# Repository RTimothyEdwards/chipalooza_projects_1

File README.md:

# Caravel Analog User

---

| :exclamation: Important Note            |
|-----------------------------------------|

This is the first test chip from the Chipalooza challenge 2024.
11 designs made it on the April tapeout.

The projects on this tapeout and their source URLs are as follows:

	1.  	High-speed crystal oscillator (4-16MHz)
		hsxo-cpz1 
		https://github.com/efabless/sky130_ht_ip__hsxo_cpz1 (forked)
		https://github.com/htfab/hsxo-cpz1
		Tamas Hubai

	2.  	Brownout detector
		sky130_ajc_ip__brownout
		https://github.com/efabless/sky130_ajc_ip__brownout (forked)
		https://github.com/ajcci/sky130_ajc_ip__brownout
		Robin Tsang

	3.  	Overvoltage detector
		sky130_ajc_ip__overvoltage
		https://github.com/efabless/sky130_ajc_ip__overvoltage (forked)
		https://github.com/ajcci/sky130_ajc_ip__overvoltage
		Robin Tsang

	4.  	Power-on-Reset
		sky130_ajc_ip__por
		https://github.com/efabless/sky130_ajc_ip__por (forked)
		https://github.com/ajcci/sky130_ajc_ip__por
		Robin Tsang

	5.  	Comparator
		sky130_ak_ip__comparator
		https://github.com/efabless/sky130_ak_ip__comparator (forked)
		https://github.com/andrewkkang/sky130_ak_ip__comparator
		Andrew Kang

	6.  	Low-speed crystal oscillator (32kHz)
		sky130_be_ip__lsxo
		https://github.com/efabless/sky130_be_ip__lsxo (forked)
		https://github.com/b-etz/sky130_be_ip__lsxo
		Brady Etz

	7.  	Temperature sensor
		sky130_od_ip__tempsensor
		https://github.com/efabless/sky130_od_ip__tempsensor (forked)
		https://github.com/ordicker/sky130_od_ip__tempsensor
		Or Dicker

	8.  	Low power operational amplifier
		sky130_rodovalho_ip__lpopamp
		https://github.com/efabless/sky130_rodovalho_ip__lpopamp (forked)
		https://github.com/lhrodovalho/sky130_rodovalho_ip__lpopamp
		Luis Henrique Rodovalho

	9.  	High gain-bandwidth operational amplifier
		sky130_td_ip__opamp_hp
		https://github.com/efabless/sky130_td_ip__opamp_hp (forked)
		https://github.com/tdextrous/sky130_td_ip__opamp_hp
		Thomas Dexter

	10. 	Overvoltage detector
		sky130_vbl_ip__overvoltage
		https://github.com/efabless/sky130_vbl_ip__overvoltage (forked)
		https://github.com/LDFranck/sky130_vbl_ip__overvoltage
		Lucas Franck, William Orlato, and Toni Tejada

	11.	Bandgap (not from Chipalooza)
		bandgap
		https://github.com/efabless/sky130_cw_ip (forked)
		https://github.com/christoph-weiser/mpw7
		Christoph Weiser

	12.	Power FET (not from Chipalooza)
		power_stage
		(in this repository)
		Weston Braun

	13.	Bias current generator (not from Chipalooza)
		bias_generator
		(in this repository)
		Tim Edwards

	14.	Ground-isolated analog switch (not from Chipalooza)
		isolated_switch_ena1v8
		(in this repository)
		Tim Edwards

(Documentation, including test instructions, still needs to be completed)

:---: | :---

Building:

Get the dependencies above by doing "make get_ip_blocks" in the top level
directory.  This will clone all of the IP blocks from various github
repository sources into the "dependencies" directory.

The test chip is generated in magic by running magic in the mag/ directory
and issuing the command "source construct_testchip.tcl".

Verifying:

In the top level directory, do "make run-precheck".  This requires at
least setting environment variables PDK_ROOT, PDK, and PRECHECK_ROOT.
If the PDK is installed with open_pdks, then PRECHECK_ROOT can be set
to open_pdks/sources/precheck_sky130.

This might take an hour. If you just want to see the results then you
can download [a tar of the full output](https://github.com/qpwo/_patch_chipalooza_projects_1/releases/tag/build4d31885)

Testing:

All projects are connected either to the logic analyzer (128 I/O bits) or
the GPIO pins.  Generally speaking, static control bits (enable and trim,
for example) are logic analyzer outputs.  Dynamic digital bits are routed
to GPIO digital outputs, while analog I/O are routed to the analog
connections of the GPIO.

Each power supply is routed through gated power pFETs so each project
can be powered individually.  Each power supply connection internally
is routed to a bare analog pin for monitoring the supply voltage of
the project.  Be aware that these are ESD-sensitive points!

Power supplies are enabled through a differential switch.  Due to
time constraints, the differential signals (enable, !enable) were
both routed to the logic analyzer.  Both bits need to be set
correctly.

Most projects take current biases which are distributed by a central
bias current generator circuit.  Various test point bias currents are
connected through ground-isolated switches to GPIO analog signals.

Project circuit blocks are described below, starting at the top left
corner of the chip and working counterclockwise around the chip
perimeter.

---

High Gain-Bandwidth Operational Amplifier  
(Thomas Dexter)  
Enable:  la_data_in[37]  
Bias:    100nA	when selected  
	Selection: la_data_in[40] = 0  
Upstream analog power supply: vdda2/vssa2  
Upstream digital power supply: vccd2/vssd2  
Power supply monitor:  io_analog[10] (pin GPIO 24) "mon_hgbw_opamp"  
Power supply enable: la_data_in[60]  
Amp output:  gpio_noesd[7] (pin GPIO 25) "hgbw_opamp_out"  
Amp negative input: gpio_analog[8] (pin GPIO 26) "hgbw_opamp_in-" when selected  
	Selection: la_data_in[36] = 1  
Amp positive input: gpio_analog[9] (pin GPIO 27) "hgbw_opamp_in+" when selected  
	Selection: la_data_in[34] = 1  

---

Temperature sensor  
(Or Dicker)  
Enable: la_data_in[35]  
Bias:  gpio_noesd[2] (pin GPIO 9) "1.2V_bias" (nominally 1.2V) when selected  
	Selection: la_data_in[122] = 1  
Upstream digital power supply: vccd2/vssd2  
Power supply monitor: io_analog[9] (pin GPIO 23) "mon_temp_sense"  
Power supply enable: la_data_in[58]  
Vbe1_out: gpio_analog[9] (pin GPIO 27) "temp_sense_vbe1" when selected  
	Selection: la_data_in[34] = 0  
Vbe2_out: gpio_analog[8] (pin GPIO 26) "temp_sense_vbe2" when selected  
	Selection: la_data_in[36] = 0  

---

Comparator  
(Andrew Kang)  
Enable: la_data_in[28]  
Hysteresis: la_data_in[29:30]  
Trim: la_data_in[25:27],la_data_in[33:31]  
Bias:	400nA	when selected  
	Selection:  la_data_in[44] = 0  
Upstream analog power supply: vdda2/vssa2  
Upstream digital power supply: vccd2/vssd2  
Power supply monitor: io_analog[8] (pin GPIO 22) "mon_comparator"  
Power supply enable: la_data_in[56]  
Comparator output: io_out[17] (pin GPIO 28) "comparator_out"  
Comparator negative input:  gpio_analog[12] (pin GPIO 30) "comparator_in-" when selected  
	Selection: la_data_in[22] = 1  
Comparator positive input:  gpio_analog[11] (pin GPIO 29) "comparator_in+" when selected  
	Selection: la_data_in[23] = 1  
	
---

Low power operational amplifier  
(Luis Henrique Rodovalho)  
Enable: la_data_in[21]  
Bias:  10uA when selected  
	Selection:  la_data_in[46] = 0  
Upstream analog power supply: vdda2/vssa2  
Upstream digital power supply: vccd2/vssd2  
Power supply monitor: io_analog[7] (pin GPIO 21) "mon_lpopamp"  
Power supply enable: la_data_in[54]  
Amplifier output:  gpio_analog[13] (pin GPIO 31) "lpopamp_out"  
Amplifier negative input: gpio_analog[11] (pin GPIO 29) "lpopamp_in-" when selected  
	Selection: la_data_in[23] = 0  
Amplifier positive input: gpio_analog[12] (pin GPIO 30) "lpopamp_in+" when selected  
	Selection: la_data_in[22] = 0  

---

High speed crystal oscillator  
(Tamas Hubai)  
Enable: la_data_in[19]  
Standby: la_data_in[20]  
Bias:  10uA when selected  
	Selection: la_data_in[47] = 0  
Upstream analog power supply: vdda2/vssa2  
Upstream digital power supply: vccd2/vssd2  
Power supply monitor: io_analog[6] (pin GPIO 20) "mon_hsxo"  
Power supply enable:  la_data_in[52]  
Oscillator out:  io_out[23] (pin GPIO 34) "hsxo_out"  
Crystal Xin:  gpio_analog[14] (pin GPIO 32) "hsxo_xin"  
Crystal Xout: gpio_analog[15] (pin GPIO 33) "hsxo_xout"  

---

Bandgap (Christoph Weiser)  
Enable: none (enable via power supply)  
Bias:  self-biased  
Trim: la_data_in[9,8,10,7,11,6,12,5,13,4,14,3,15,2,16,1]  
Upstream digital power supply: vccd2/vssd2  
Power supply monitor: io_analog[5] (pin GPIO 19) "mon_bandgap"  
Power supply enable: la_data_in[50]  
Bandgap output:  gpio_analog[16] (pin GPIO 34) "bandgap_out" when selected  
	Selection:  la_data_in[18] = 1  

---

Brownout detector (Robin Tsang)  
Enable: la_data_in[109]  
Bias: gpio_noesd[2] (pin GPIO 9) "1.2V_bias" (nominally 1.2V) when selected  
	Selection: la_data_in[122] = 0  
Bias: 200nA when selected  
	Selection: la_data_in[43] = 0  
Trip point select (otrip):  la_data_in[112:113,111]  
Trip point select (vtrip):  la_data_in[107:106,108]  
Force enable RC osc: la_data_in[115]  
Force disable RC osc: la_data_in[114]  
Force short oneshot: la_data_in[116]  
Current source select: la_data_in[110]  
Upstream analog power supply: vdda1/vssa1  
Upstream digital power supply: vccd1/vssd1  
Power supply monitor: io_analog[0] (pin GPIO 14) "mon_brownout"  
Power supply enable: la_data_in[77]  
Outb: io_out[0] (pin GPIO 0) "brownout_outb"  
Dcomp: io_out[1] (pin GPIO 1) "brownout_dcomp"  
Vunder: io_out[5] (pin GPIO 5) "brownout_vunder"  
Timed out: la_data_out[117]  

---

Overvoltage detector (Robin Tsang)  
Enable: la_data_in[100]  
Bias: gpio_noesd[2] (pin GPIO 9) "1.2V_bias" (nominally 1.2V) when selected  
	Selection: la_data_in[122] = 0  
Bias: 200nA when selected  
	Selection: la_data_in[42] = 0  
Trip point select (otrip):  la_data_in[105:102]  
Current source select: la_data_in[101]  
Upstream analog power supply: vdda1/vssa1  
Upstream digital power supply: vccd1/vssd1  
Power supply monitor: io_analog[1] (pin GPIO 15) "mon_overvoltage1"  
Power supply enable: la_data_in[75]  
Ovout: io_out[6] (pin GPIO 6) "overvoltage1_ovout"  

---

Power-on-reset (Robin Tsang)  
Bias: gpio_noesd[2] (pin GPIO 9) "1.2V_bias" (nominally 1.2V) when selected  
	Selection: la_data_in[122] = 0  
Bias: 200nA when selected  
	Selection: la_data_in[41] = 0  
Trip point select (otrip): la_data_in[96:98]  
Force PDN: la_data_in[94]  
Force enable RC osc: la_data_in[93]  
Force disable RC osc: la_data_in[92]  
Force short oneshot: la_data_in[99]  
Current source select: la_data_in[95]  
Upstream analog power supply: vdda1/vssa1  
Upstream digital power supply: vccd1/vssd1  
Power supply monitor: io_analog[2] (pin GPIO 16) "mon_por"  
Power supply enable: la_data_in[73]  
POR: io_out[7] (pin GPIO 7) "por_out"  
PORb: io_out[8] (pin GPIO 8) "por_outb"  
Osc_clk: io_out[3] (pin GPIO 3) "por_osc_clk"  
Dcomp: io_out[2] (pin GPIO 2) "por_dcomp"  
Pwup_filt: io_out[4] (pin GPIO 4) "por_pwup_filt"  
Startup timed out: la_data_out[120]  
POR timed out: la_data_out[119]  

---

Low-speed (32kHz) crystal oscillator (Brady Etz)  
Enable: la_data_in[86]  
Standby: la_data_in[85]  
Bias: 50nA when selected  
	Selection: la_data_in[39] = 0  
Upstream analog power supply: vdda1/vssa1  
Upstream digital power supply: vccd1/vssd1  
Power supply monitor: io_analog[3] (pin GPIO 17) "mon_lsxo"  
Power supply enable: la_data_in[69]  
Dout: io_out[12] (pin GPIO 12) "lsxo_out"  
Crystal XIn: gpio_noesd[3] (pin GPIO 10) "lsxo_xin"  
Crystal XOut: gpio_noesd[4] (pin GPIO 11) "lsxs_xout"  

---

Overvoltage detector (Lucas Franck & William Orlato)  
Enable: la_data_in[91]  
Bias: gpio_noesd[2] (pin GPIO 9) "1.2V_bias" (nominally 1.2V) when selected  
	Selection: la_data_in[122] = 1  
Bias: 600nA when selected  
	Selection: la_data_in[45] = 0  
Trip point select (vtrip): la_data_in[87:90]  
Upstream analog power supply: vdda1/vssa1  
Upstream digital power supply: vccd1/vssd1  
Power supply monitor: io_analog[4] (pin GPIO 18) "mon_overvoltage2"  
Power supply enable: la_data_in[65]  
OVout: io_out[13] (pin GPIO 13) "overvoltage2_out"  

---

All bias currents are regulated by an input bias voltage which is
nominally 3.3V but may be adjusted up or down to trim the bias
(limit max. voltage VDDIO + 0.3V to avoid forward biasing the ESD
diodes into the power supply).  
Bias in: gpio_analog[17] (pin GPIO 35) "bias_trim_in"  

---

Three power FETs are unused but should be kept disabled:  
Enable:  la_data_in[62], la_data_in[67], la_data_in[71]  

---

The bias generator has a master enable signal that will enable
all bias currents:  

Enable bias generator:  la_data_in[79]   

It also has a separate disable signal for the sources (which is
all of the biases used by projects on this chip):  

Disable bias generator sources:  la_data_in[48]   

---

These current sources/sinks are multiplexed to analog pins not otherwise
being used for projects.  The "enable" or "disable" bit enables or disables
the current bias, and "selection" connects it to the associated pin:  

100nA source (test0): gpio_analog[16] (pin GPIO 34) when selected  
	Disable: la_data_in[49]  
	Selection: la_data_in[18] = 0 (at pin)  

100nA source (test1): gpio_analog[10] (pin GPIO 28) when selected  
	Disable: la_data_in[38]  
	Selection: la_data_in[17] = 1 (at pin)  

100nA sink (test1): gpio_analog[6] (pin GPIO 13) when selected  
	Enable:  la_data_in[84]  
	Selection: la_data_in[124] = 1 (at pin)  

3.7uA sink (sink_3700): gpio_analog[5] (pin GPIO 12) when selected  
	Enable:  la_data_in[83]  
	Selection: la_data_in[123] = 1 (at pin)  

5.0uA sink (sink_5000_1): gpio_analog[1] (pin GPIO 8) when selected  
	Enable:  la_data_in[81]  
	Selection: la_data_in[121] = 1 (at pin)  

100nA sink (test0): gpio_analog[0] (pin GPIO 7) when selected  
	Enable:  la_data_in[78]  
	Selection: la_data_in[118] = 1 (at pin)  

---

Refer to [README](docs/source/index.rst) for this sample project documentation.   

Refer to docs/chipalooza_testchip1.pdf (.ps) for a package pinout drawing.  

---

Chip QFN-64 package pinout:

Pin  Signal(s)  
 1   vssa2  
 2   mprj_io[25] hgbw_opamp_out  
 3   mprj_io[26] hgbw_opamp_in- temp_sense_vbe2  
 4   mprj_io[27] hgbw_opamp_in+ temp_sense_vbe1  
 5   mprj_io[28] comparator_out source_100_1  
 6   mprj_io[29] comparator_in+ lpopamp_in-  
 7   mprj_io[30] comparator_in- lpopamp_in+  
 8   mprj_io[31] lpopamp_out  
 9   vdda2  
10   vssd2  
11   mprj_io[32] hsxo_xin  
12   mprj_io[33] hsxo_xout  
13   mprj_io[34] hsxo_out  bandgap_out source_100_0  
14   mprj_io[35] bias_trim_in  
15   mprj_io[36]  
16   mprj_io[37]  
17   vddio  
18   vccd  
19   N/C  
20   vssa  
21   resetb  
22   clock  
23   vssd  
24   flash_csb  
25   flash_clk  
26   flash_io0  
27   flash_io1  
28   gpio  
29   vssio  
30   vdda  
31   mprj_io[0] brownout_outb  
32   mprj_io[1] brownout_dcomp  
37   mprj_io[2] por_dcomp  
34   mprj_io[3] por_osc_clk  
35   mprj_io[4] por_pwup_filt  
36   mprj_io[5] brownout_vunder  
37   mprj_io[6] overvoltage1_ovout  
38   vssa1  
39   vssd1  
40   vdda1  
41   mprj_io[7] por_out  sink_100_0  
42   mprj_io[8] por_outb  
43   mprj_io[9]  1.2V_bias  
44   mprj_io[10] lsxo_xin  
45   mprj_io[11] lsxo_xout  
46   mprj_io[12] lsxo_out  sink_3700  
47   vdda1  
48   mprj_io[13] overvoltage2_out  sink_100_1  
49   vccd1  
50   mprj_io[14] mon_brownout  
51   mprj_io[15] mon_overvoltage1  
52   vssa1  
53   mprj_io[16] mon_por  
54   mprj_io[17] mon_lsxo  
55   mprj_io[18] mon_overvoltage2  
56   vssio  
57   mprj_io[19] mon_bandgap  
58   mprj_io[20] mon_hsxo  
59   mprj_io[21] mon_lpopamp  
60   mprj_io[22] mon_comparator  
61   mprj_io[23] mon_temp_sense  
62   mprj_io[24] mon_hgbw_opamp  
63   vccd2  
64   vddio  

---

NOTES:  The following pins have dual analog and digital functions.  The
analog function is enabled/disabled by a ground isolation swtch, and the
digital function is enabled/disabled by configuring the GPIO from
software.

pin 41:  por_out (digital), sink_100_0 (analog)  
pin 42:  porb_out (digital), sink_5000_1 (analog)  
pin 46:  lsxo_out (digital), sink_3700 (analog)  
pin 5:   comparator_out (digital), source_100_1 (analog)  
pin 13:  hsxo_out (digital), bandgap_out, source_100_0 (analog, multiplexed)*  

*Because the analog on pin 13 is multiplexed, the analog can only be
 completely disabled by selecting source_100_0 as the multiplexer input and
 then disabling the current source.  This is not ideal but should not
 interfere with the HSXO output.

---

Logic analyzer map:

la_data_in[16:1]  Bandgap trim (not in order)  
la_data_in[17]	  Select source_test_1 at pin  
la_data_in[18]    Select bandgap_out (1) or source_test_0 (0)  
la_data_in[19]	  HSXO enable  
la_data_in[20]	  HSXO standby  
la_data_in[21]	  LP opamp enable  
la_data_in[22]	  Select comparator_in- (1) or lpopamp_in+ (0)  
la_data_in[23]	  Select comparator_in+ (1) or lpopamp_in- (0)  
la_data_in[27:25] Comparator trim  
la_data_in[28]	  Comparator enable  
la_data_in[30:29] Comparator hysteresis  
la_data_in[33:31] Comparator trim  
la_data_in[34]	  Select hgbw_opamp_in+ (1) or temp_sense_vbe1 (0)  
la_data_in[35]	  Temperature sensor enable  
la_data_in[36]	  Select hgbw_opamp_in- (1) or temp_sense_vbe2 (0)  
la_data_in[37]	  HGBW op amp enable  
la_data_in[38]	  Disable source_test_1 at bias  
la_data_in[39]	  Disable LSXO 50nA bias  
la_data_in[40] 	  Disable HGBW op amp 100nA bias  
la_data_in[41] 	  Disable POR 200nA bias  
la_data_in[42]	  Disable Overvoltage1 200nA bias  
la_data_in[43]	  Disable Brownout 200nA bias  
la_data_in[44]	  Disable Comparator 400nA bias  
la_data_in[45]	  Disable Overvoltage2 600nA bias  
la_data_in[46]	  Disable LP op amp 10uA bias  
la_data_in[47]	  Disable HSXO 10uA bias  
la_data_in[48] 	  Disable bias generator sources  
la_data_in[49]	  Disable source_test_0  
la_data_in[50]	  Enable Bandgap power supply  
la_data_in[52]	  Enable HSXO power supply  
la_data_in[54]	  Enable LP op amp power supply  
la_data_in[56]	  Enable Comparator power supply  
la_data_in[58]	  Enable Temperature sensor power supply  
la_data_in[60]	  Enable HGBW op amp power supply  
la_data_in[62]	  (Enable unused power supply)  
la_data_in[65]	  Enable Overvoltage2 power supply  
la_data_in[67]	  (Enable unused power supply)  
la_data_in[69]	  Enable LSXO power supply  
la_data_in[71]	  (Enable unused power supply)  
la_data_in[73]	  Enable POR power supply  
la_data_in[75]	  Enable Overvoltage1 power supply  
la_data_in[77]	  Enable Brownout power supply  
la_data_in[78]	  Enable sink_test_0  
la_data_in[79]	  Enable bias generator (master enable)  
la_data_in[80]	  Enable sink_5000_0 (unused)  
la_data_in[81]	  Enable sink_5000_1  
la_data_in[82]	  Enable sink_5000_2 (unused)  
la_data_in[83]	  Enable sink_3700  
la_data_in[84]	  Enable sink_test_1  
la_data_in[85]    LSXO Standby  
la_data_in[86]    LSXO Enable  
la_data_in[90:87] Overvoltage2 trip point selection  
la_data_in[91]	  Overvoltage2 enable  
la_data_in[92]	  POR force disable RC oscillator  
la_data_in[93]	  POR force enable RC oscillator  
la_data_in[94]	  POR force PDN  
la_data_in[95]	  POR current source select  
la_data_in[98:96] POR trip point select  
la_data_in[99]	  POR force short oneshot  
la_data_in[100]	  Overvoltage1 enable  
la_data_in[101]	  Overvoltage1 current source select  
la_data_in[105:102] Overvoltage1 trip point select  
la_data_in[108:106] Brownout trip point (vtrip) select  
la_data_in[109]	  Brownout enable  
la_data_in[110]	  Brownout current source select  
la_data_in[113:111] Brownout trip point (otrip) select  
la_data_in[114]	  Brownout force disable RC oscillator  
la_data_in[115]	  Brownout force enable RC oscillator  
la_data_in[116]	  Brownout force short oneshot  
la_data_out[117]  Brownout timed out  
la_data_in[118]	  Select sink_test_0 at pin  
la_data_out[119]  POR timed out  
la_data_out[120]  POR startup timed out  
la_data_in[121]	  Select sink_5000_1 at pin  
la_data_in[122]	  Select 1.2V bias (see above)  
la_data_in[123]	  Select sink_3700 at pin  
la_data_in[124]	  Select sink_test_1 at pin  
la_data_in[125]	  Enable sink_2000 (unused)  

---

Test plan:

Write a software routine to run on flash that communicates via UART.
Because projects use GPIO[1-4] (housekeeping SPI) and GPIO[5-6] (UART),
use pin GPIO[36] to toggle between the UART and project I/O, and use
pin GPIO[37] to toggle between the housekeeping SPI and project I/O.
Program should communicate with the host computer to select and
identify projects, and to set trim and other configuration bits as
needed.

For helping with testbench scripting, an API has been defined in
the `firmware/` directory.  File `chipalooza_defs.h` define all of the
bit mask values into the logic analyzer data arrays.  File
`chipalooza_utils.c` defines a set of routines for accessing each
of the projects.  Note that this only defines access to each project
for the configuration that is set or read from the logic analyzer
data array.  Check the connections of each project referenced above
for information on what I/O pins to connect to for each project,
which power supplies need to be enabled, and any other board-level
inputs or outputs required.

chipalooza_utils.c API:

Bandgap:

	void bandgap_powerup()

	void bandgap_powerdown()

	void bandgap_select_output()

	void bandgap_set_trim(uint16_t value)

HSXO:

	void hsxo_powerup()

	void hsxo_powerdown()

	void hsxo_enable()

	void hsxo_disable()

	void hsxo_run()

	void hsxo_standby()

	void hsxo_bias_enable()

	void hsxo_bias_disable()

LSXO:

	void lsxo_powerup()

	void lsxo_powerdown()

	void lsxo_enable()

	void lsxo_disable()

	void lsxo_run()

	void lsxo_standby()

	void lsxo_bias_enable()

	void lsxo_bias_disable()

LP opamp:

	void lp_opamp_powerup()

	void lp_opamp_powerdown()

	void lp_opamp_enable()

	void lp_opamp_disable()

	void lp_opamp_enable_inputs()

	void lp_opamp_bias_enable()

	void lp_opamp_bias_disable()

Comparator:

	void comparator_powerup()

	void comparator_powerdown()

	void comparator_enable()

	void comparator_disable()

	void comparator_enable_inputs()

	void comparator_bias_enable()

	void comparator_bias_disable()

	void comparator_set_hyst(uint8_t value)

	void comparator_set_trim(uint8_t value)

Temperature sensor:

	void tempsense_powerup()

	void tempsense_powerdown()

	void tempsense_enable()

	void tempsense_disable()

	void tempsense_enable_outputs()

HGBW op-amp:

	void hgbw_opamp_powerup()

	void hgbw_opamp_powerdown()

	void hgbw_opamp_enable()

	void hgbw_opamp_disable()

	void hgbw_opamp_enable_inputs()

	void hgbw_opamp_bias_enable()

	void hgbw_opamp_bias_disable()

Overvoltage detector (2):

	void overvoltage2_powerup()

	void overvoltage2_powerdown()

	void overvoltage2_enable()

	void overvoltage2_disable()

	void overvoltage2_bias_enable()

	void overvoltage2_bias_disable()

	void overvoltage2_set_trippoint(uint8_t value)

POR:

	void por_powerup()

	void por_powerdown()

	void por_vbg_enable()

	void por_vbg_disable()

	void por_bias_enable()

	void por_bias_disable()

	void por_osc_default()

	void por_force_osc_on()

	void por_force_osc_off()

	void por_pdn_default()

	void por_force_pdn()

	void por_select_external_bias()

	void por_select_internal_bias()

	void por_oneshot_mode()

	void por_continuous_mode()

	void por_set_trippoint(uint8_t value)

	uint8_t por_get_timeout()

	uint8_t por_get_startup_timeout()

Overvoltage detector (1):

	void overvoltage1_powerup()

	void overvoltage1_powerdown()

	void overvoltage1_enable()

	void overvoltage1_disable()

	void overvoltage1_bias_enable()

	void overvoltage1_bias_disable()

	void overvoltage1_select_external_bias()

	void overvoltage1_select_internal_bias()

	void overvoltage1_set_trippoint(uint8_t value)

Brownout detector:

	void brownout_powerup()

	void brownout_powerdown()

	void brownout_vbg_enable()

	void brownout_vbg_disable()

	void brownout_bias_enable()

	void brownout_bias_disable()

	void brownout_select_external_bias()

	void brownout_select_internal_bias()

	void brownout_set_vtrippoint(uint8_t value)

	void brownout_set_otrippoint(uint8_t value)

	void brownout_osc_default()

	void brownout_force_osc_on()

	void brownout_force_osc_off()

	void brownout_oneshot_mode()

	void brownout_continuous_mode()

	uint8_t brownout_get_timeout()

Bias generator:

	void biasgen_enable()

	void biasgen_disable()

	void biasgen_sources_enable()

	void biasgen_sources_disable()

Bias generator test outputs:

	void biasgen_source_test0_enable()

	void biasgen_source_test0_disable()

	void biasgen_source_test0_enable_output()

	void biasgen_source_test0_disable_output()

	void biasgen_source_test1_enable()

	void biasgen_source_test1_disable()

	void biasgen_source_test1_enable_output()

	void biasgen_source_test1_disable_output()

	void biasgen_sink_test0_enable()

	void biasgen_sink_test0_disable()

	void biasgen_sink_test0_enable_output()

	void biasgen_sink_test0_disable_output()

	void biasgen_sink_test1_enable()

	void biasgen_sink_test1_disable()

	void biasgen_sink_test1_enable_output()

	void biasgen_sink_test1_disable_output()

	void biasgen_sink_test_3700_enable()

	void biasgen_sink_test_3700_disable()

	void biasgen_sink_test_3700_enable_output()

	void biasgen_sink_test_3700_disable_output()

	void biasgen_sink_test_5000_enable()

	void biasgen_sink_test_5000_disable()

	void biasgen_sink_test_5000_enable_output()

	void biasgen_sink_test_5000_disable_output()

Power switching:

	void powerdown_unused()

	void powerdown_all()

General:

	void init_logic_analyzer()

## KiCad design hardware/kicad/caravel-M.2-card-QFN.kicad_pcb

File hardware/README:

The LSXO and HSXO on the test chip will perform poorly unless the
crystals and their load caps are placed close to the package pins
where the crystal inputs and outputs are located.  The existing
M.2 daughtercard for the chipIgnite development board does not
have pads for additional components.

This alternative daughter card is specifically for use with this
project and has pads for the low speed (32kHz) crystal on the
front side (X2), and pads for a surface mount high-speed crystal
(8-16 MHz) on the back side (X1) with a footprint that will
accommodate several sizes (2x1.6, 2.5x2, or 3.2x2.5).  For the
lower speeds (4 and 6 MHz), an additonal through-hole mount
(X3) is provided (requires zero-ohm resistors on JP1 and JP2).

Thanks to Brady Etz (who designed the LSXO for Chipalooza) for
the daughterboard design.

For the LSXO:
Suggested vendor:  Mouser Electronics
Suggested parts:
	ECS-.327-12.5-12R-C [CL=12.5pF]
	LFXTAL062558 [CL=9pF]
	ABS06-32.768KHZ-6-1 [CL=6pF]

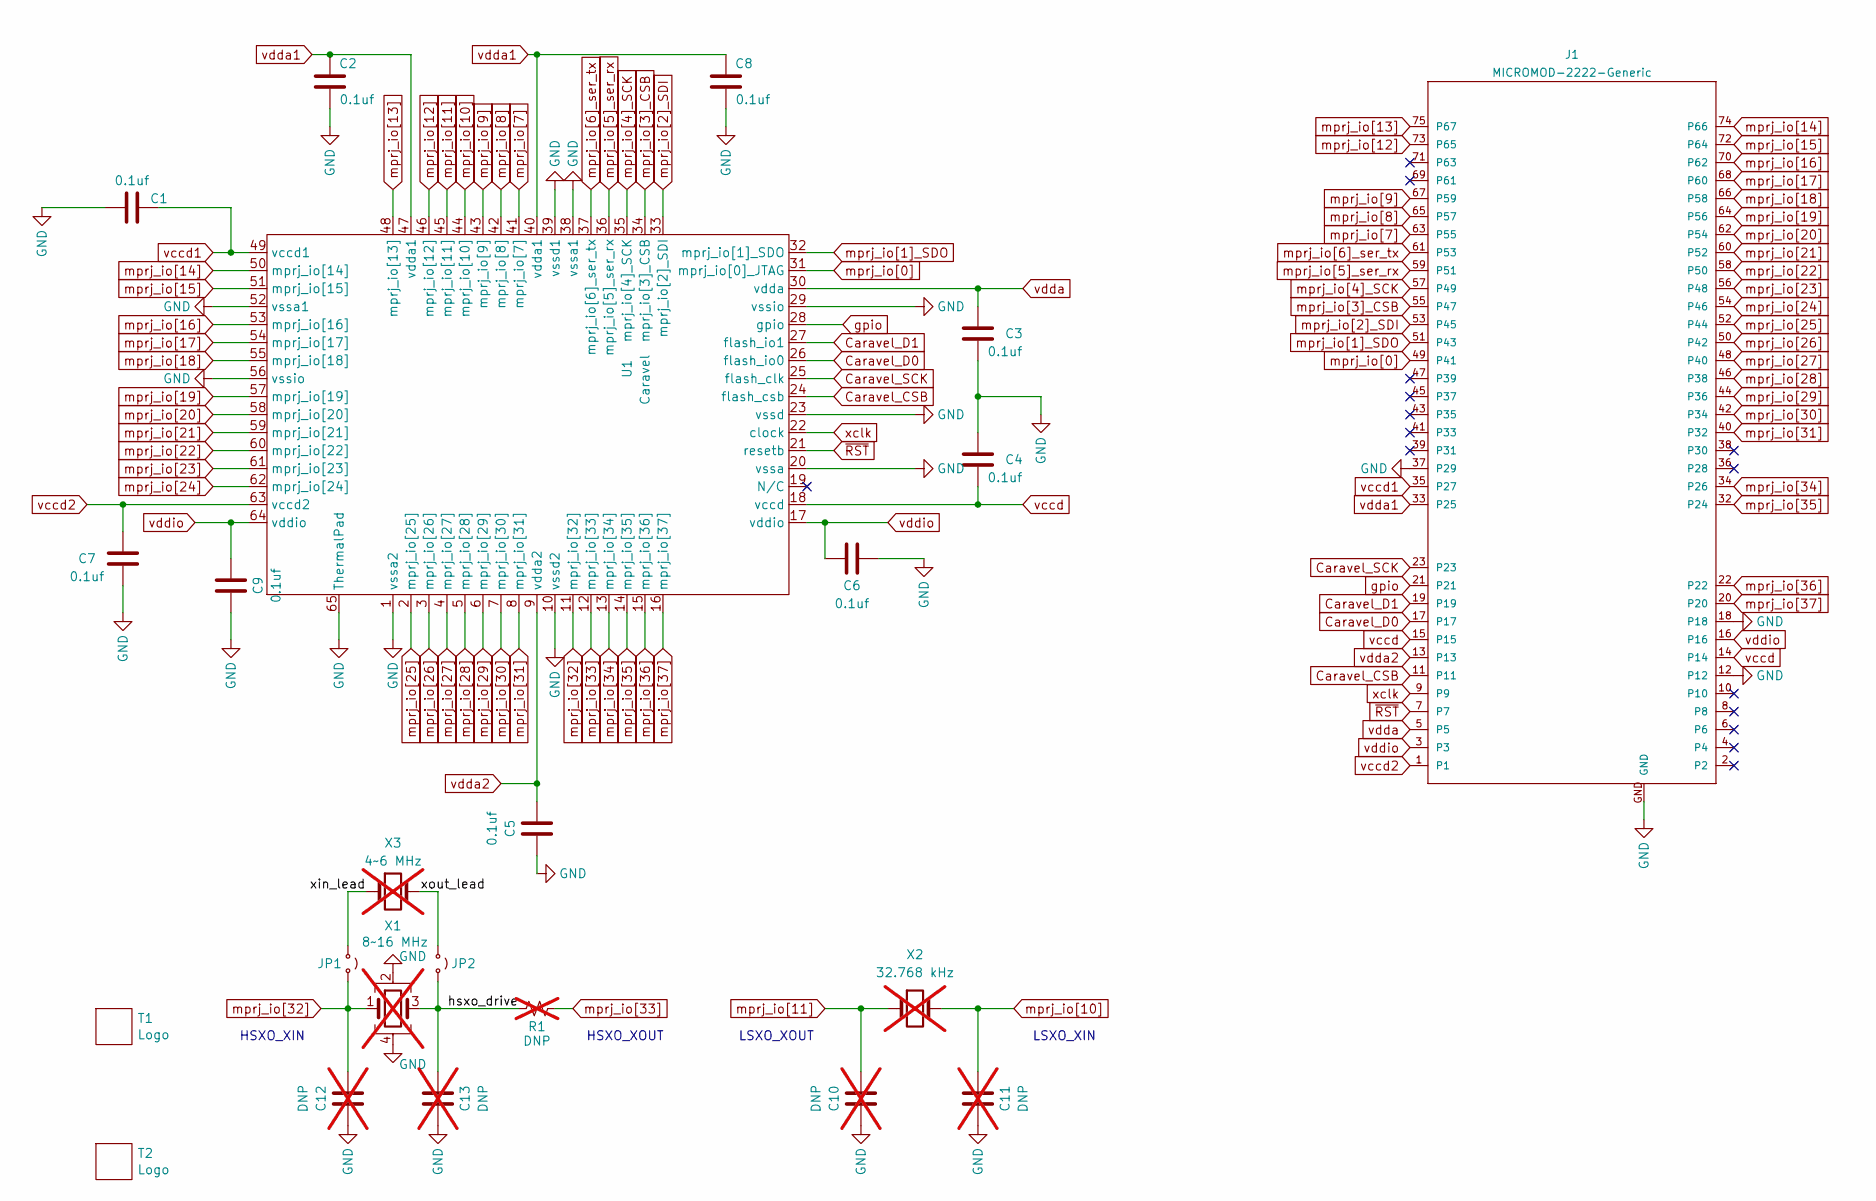
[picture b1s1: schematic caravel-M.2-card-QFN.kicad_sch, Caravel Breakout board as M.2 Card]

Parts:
C1, C2, C3, C4, C5, C6, C7, C8, C9: 0.1uf; C_0402_1005Metric
C10, C11: DNP; C_0402_1005Metric; not fitted
C12, C13: DNP; C_0402_1005Metric_Pad0.74x0.62mm_HandSolder; not fitted
J1: MICROMOD-2222-Generic; MicroMod-M.2-CARD-E-22
JP1, JP2: Jumper_2_Small_Open; Fuse_0402_1005Metric
R1: DNP; R_0402_1005Metric_Pad0.72x0.64mm_HandSolder; not fitted
T1: Logo; logo_small
T2: Logo; ef_logo
U1: Caravel; QFN-64-1EP_9x9mm_P0.5mm_EP7.65x7.65mm
X1: 8~16 MHz; Crystal_SMD_3225-4Pin_3.2x2.5mm; not fitted
X2: 32.768 kHz; Crystal_SMD_2012-2Pin_2.0x1.2mm; not fitted
X3: 4~6 MHz; Crystal_HC49-U_Vertical; not fitted

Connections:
/hsxo_drive: C13.1, JP2.2 (B), R1.1, X1.3
/xin_lead: JP1.1 (A), X3.1
/xout_lead: JP2.1 (A), X3.2
Caravel_CSB: J1.11, U1.24 (flash_csb)
Caravel_D0: J1.17, U1.26 (flash_io0)
Caravel_D1: J1.19, U1.27 (flash_io1)
Caravel_SCK: J1.23, U1.25 (flash_clk)
GND: C1.1, C2.2, C3.2, C4.1, C5.1, C6.1, C7.1, C8.2, C9.1, C10.1, C11.2, C12.1, C13.2, J1.12, J1.18, J1.37 (P29), J1.GND, U1.1 (vssa2), U1.10 (vssd2), U1.20 (vssa), U1.23 (vssd), U1.29 (vssio), U1.38 (vssa1), U1.39 (vssd1), U1.52 (vssa1), U1.56 (vssio), U1.65 (ThermalPad), X1.2, X1.4
gpio: J1.21, U1.28 (gpio)
mprj_io[0]: J1.49 (P41), U1.31 (mprj_io[0]_JTAG)
mprj_io[1]_SDO: J1.51 (P43), U1.32 (mprj_io[1]_SDO)
mprj_io[2]_SDI: J1.53 (P45), U1.33 (mprj_io[2]_SDI)
mprj_io[3]_CSB: J1.55 (P47), U1.34 (mprj_io[3]_CSB)
mprj_io[4]_SCK: J1.57 (P49), U1.35 (mprj_io[4]_SCK)
mprj_io[5]_ser_rx: J1.59 (P51), U1.36 (mprj_io[5]_ser_rx)
mprj_io[6]_ser_tx: J1.61 (P53), U1.37 (mprj_io[6]_ser_tx)
mprj_io[7]: J1.63 (P55), U1.41 (mprj_io[7])
mprj_io[8]: J1.65 (P57), U1.42 (mprj_io[8])
mprj_io[9]: J1.67 (P59), U1.43 (mprj_io[9])
mprj_io[10]: C11.1, U1.44 (mprj_io[10]), X2.2
mprj_io[11]: C10.2, U1.45 (mprj_io[11]), X2.1
mprj_io[12]: J1.73 (P65), U1.46 (mprj_io[12])
mprj_io[13]: J1.75 (P67), U1.48 (mprj_io[13])
mprj_io[14]: J1.74 (P66), U1.50 (mprj_io[14])
mprj_io[15]: J1.72 (P64), U1.51 (mprj_io[15])
mprj_io[16]: J1.70 (P62), U1.53 (mprj_io[16])
mprj_io[17]: J1.68 (P60), U1.54 (mprj_io[17])
mprj_io[18]: J1.66 (P58), U1.55 (mprj_io[18])
mprj_io[19]: J1.64 (P56), U1.57 (mprj_io[19])
mprj_io[20]: J1.62 (P54), U1.58 (mprj_io[20])
mprj_io[21]: J1.60 (P52), U1.59 (mprj_io[21])
mprj_io[22]: J1.58 (P50), U1.60 (mprj_io[22])
mprj_io[23]: J1.56 (P48), U1.61 (mprj_io[23])
mprj_io[24]: J1.54 (P46), U1.62 (mprj_io[24])
mprj_io[25]: J1.52 (P44), U1.2 (mprj_io[25])
mprj_io[26]: J1.50 (P42), U1.3 (mprj_io[26])
mprj_io[27]: J1.48 (P40), U1.4 (mprj_io[27])
mprj_io[28]: J1.46 (P38), U1.5 (mprj_io[28])
mprj_io[29]: J1.44 (P36), U1.6 (mprj_io[29])
mprj_io[30]: J1.42 (P34), U1.7 (mprj_io[30])
mprj_io[31]: J1.40 (P32), U1.8 (mprj_io[31])
mprj_io[32]: C12.2, JP1.2 (B), U1.11 (mprj_io[32]), X1.1
mprj_io[33]: R1.2, U1.12 (mprj_io[33])
mprj_io[34]: J1.34 (P26), U1.13 (mprj_io[34])
mprj_io[35]: J1.32 (P24), U1.14 (mprj_io[35])
mprj_io[36]: J1.22, U1.15 (mprj_io[36])
mprj_io[37]: J1.20, U1.16 (mprj_io[37])
vccd: C4.2, J1.14, J1.15, U1.18 (vccd)
vccd1: C1.2, J1.35 (P27), U1.49 (vccd1)
vccd2: C7.2, J1.1, U1.63 (vccd2)
vdda: C3.1, J1.5, U1.30 (vdda)
vdda1: C2.1, C8.1, J1.33 (P25), U1.40 (vdda1), U1.47 (vdda1)
vdda2: C5.2, J1.13, U1.9 (vdda2)
vddio: C6.2, C9.2, J1.3, J1.16, U1.17 (vddio), U1.64 (vddio)
xclk: J1.9, U1.22 (clock)
~RST: J1.7, U1.21 (resetb)

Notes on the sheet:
LSXO_XOUT
HSXO_XIN
LSXO_XIN
HSXO_XOUT

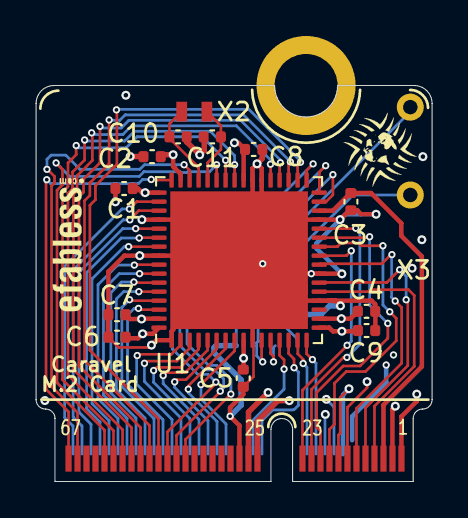
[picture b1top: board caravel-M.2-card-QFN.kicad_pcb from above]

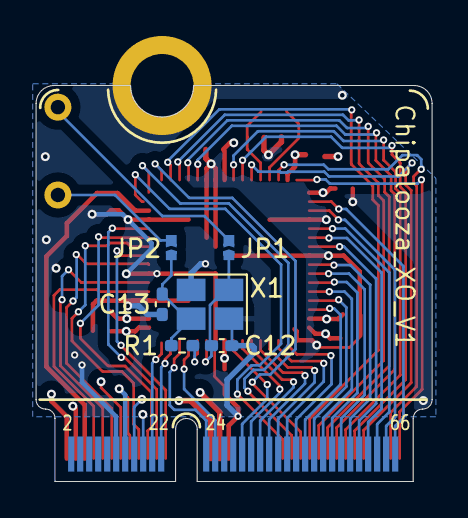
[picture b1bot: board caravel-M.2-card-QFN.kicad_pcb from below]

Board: 4 copper layers, 22.0 x 22.0 mm, 23 parts (6 on the bottom side), 56 nets.

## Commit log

2024-04-25 Uploading everything from local work. Chipalooza projects first attempt. Chip, chip, hooray!
2024-04-25 Update after LVS finished.
2024-04-25 Was too distracted trying to do a push during a zoom call last time, and failed to move the new GDS file to the gds/ directory.
2024-04-25 Rewrote the assembly script to avoid trashing the standard cells and creating invalid GDS.
2024-04-26 Update after running precheck locally and fixing all outstanding errors.
2024-04-26 Corrected one pin layer error that failed to get resolved in the last update (but was not noticed), and added the default lvs_config.json in the hopes that the run will not fail on the missing file (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
2024-04-27 Layout modifications for correcting antenna violations, and changes to possibly avoid an error on the OEB checks.
2024-04-29 Updated the README file with the complete list of digital controls and pin assignments.
2024-05-03 Updated files post-tapeout to make sure that the repository is LVS and DRC clean. Corresponds to changes made to each of the project repositories (in branches "tapeout_ci2404", pull requests to be ma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
2024-05-06 Removed the bandgap modified layouts and put them where they belong, in the repository from which they were taken. Added a Makefile target for cloning the IP block repositories locally. Reconstructed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
2024-05-07 Corrected the logic analyzer connections, which were all backwards, with la_data_out connected where la_data_in should have been, and vice versa.
2024-05-08 Changed double slashes in paths to dependencies to single slashes in chipalooza_testchip1.mag. This shouldn't be a problem but the single slash is more correct.
2024-05-08 Added a drawing of the package pinout with project pin names, and filled out the README file with additional clarifying details, such as lists ordered by package pin and by logic analyzer bit, and sp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
2024-06-05 add output tar
2024-11-22 Updating the README.md file with the intended line breaks in markdown to make it readable.
2024-11-22 Added utility code for writing firmware tests for the Chipalooza projects. Added a list of the utility routines to README.md.
2024-11-23 Added files for aiding in creating testbenches for the chipalooza projects. Includes a set of definitions for the logic analyzer bits, a set of routines for handling the logic analyzer values, and an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
2024-11-23 Added a handful of test programs that I coded up, for the bandgap, bias generator, comparator, and both operational amplifiers. All have been lightly tested for basic functionality.
2024-12-19 Added test code for the remaining analog blocks that had not previously been coded.
2024-12-29 Corrected the trip point voltage setting for the overvoltage1 circuit in chipalooza_util.c, which was truncating the 32 bit logic analyzer value to an 8-bit value.
2024-12-29 Corrected error in chipalooza_test_brownout.c that prevents compilation.
2024-12-29 Corrected an error in the setting of the enable/disable bit for the Von Braun Labs' overvoltage detector. Changed the digital input bits for setting the trim to avoid GPIO 5, which is held high by th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
2024-12-29 Corrected some code in chipalooza_test_brownout.c and added a missing routine to chipalooza_util.c to enable/disable the brownout circuit.
2025-02-15 Added directory "hardware" with (gerber) files for a special M.2 daughter card design to be used with the test chip to allow crystals to be placed close to the chip package for testing the LSXO and H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
2025-02-15 Added KiCad design files for the custom M.2 daughter card (again, thanks to Brady Etz!).

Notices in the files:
README.md:
License: Apache 2.0
